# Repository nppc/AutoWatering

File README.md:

# Periodic watering
Simple periodic watering controller
With OLED 96x16 pixels.

Two states of operation.
Waiting (configurable, max 99 hours and 59 minutes)
While waiting after 3 minutes of state change it goes to savescreen mode.
In this mode you see the random dots. Dots quantity is minutes remaining (but not more than 40 dots).

Watering (configurable, max 99 minutes and 59 seconds)
While watering low mosfet is turned on.

## Configuration
Press and hold button until wait time start blink. If you need to adjust watering time, then hold button longer.

With short presses change number 1 by 1. With long press - numbers is running.
If button is not pressed for more than 3 seconds, then next number will be available for adjust.

New time is stored in eeprom.

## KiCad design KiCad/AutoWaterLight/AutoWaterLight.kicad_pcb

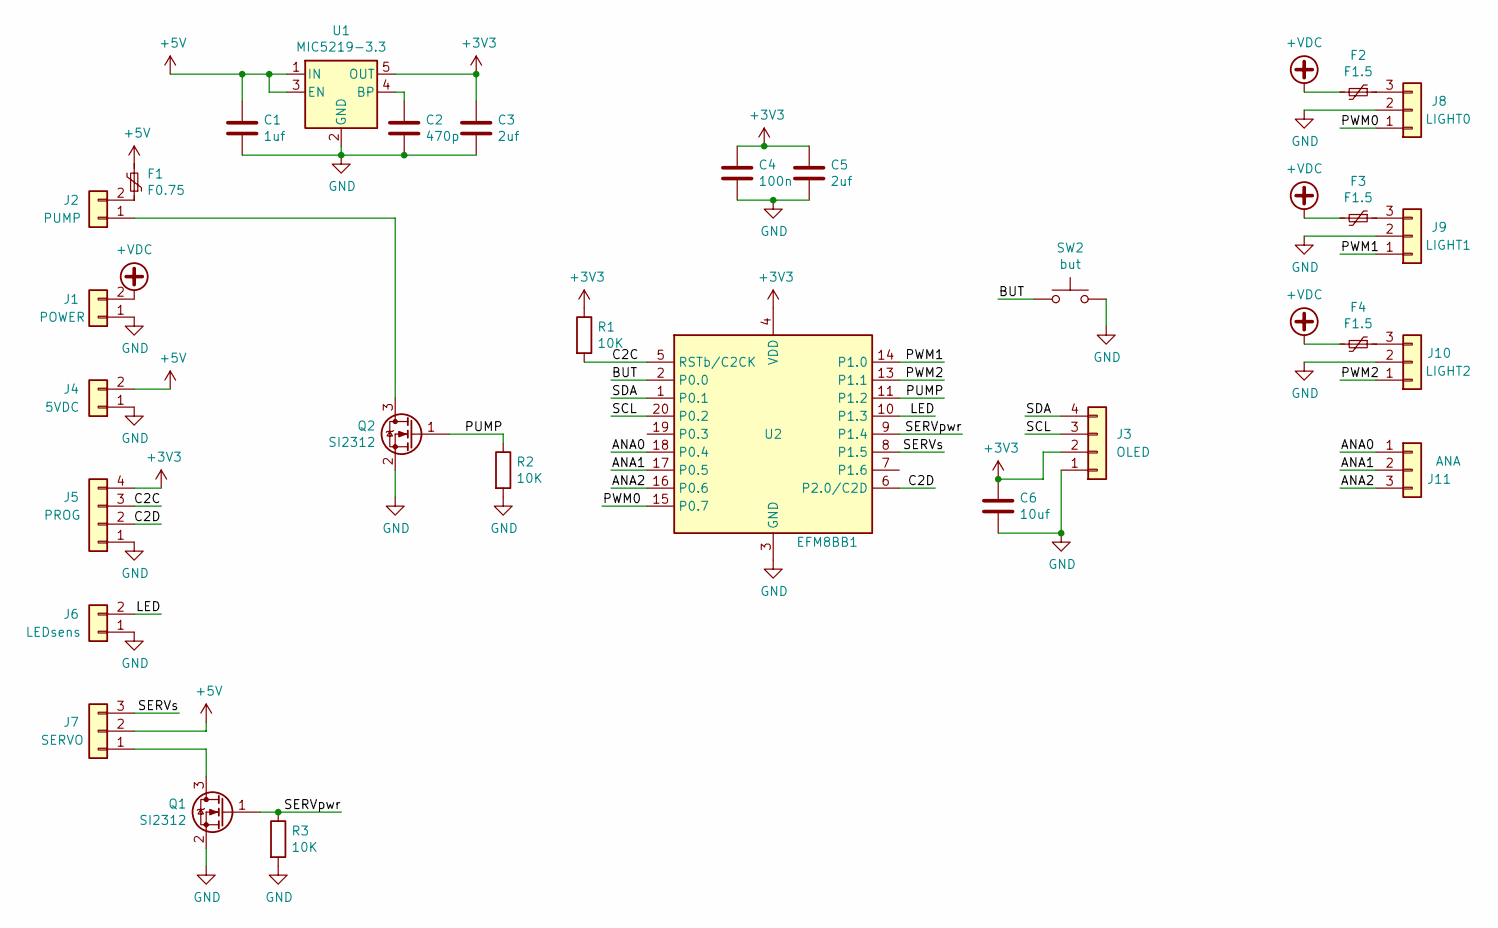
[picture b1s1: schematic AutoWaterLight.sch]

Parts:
C1: 1uf; C_0603
C2: 470p; C_0603
C3, C5: 2uf; C_0603
C4: 100n; C_0603
C6: 10uf; C_0603
F1: F0.75; R_1812
F2, F3, F4: F1.5; R_1812
J1: POWER; Conn_Power
J2: PUMP; Conn_1x02_2.54_0.9mm
J3: OLED; Pin_Header_Straight_1x04_Pitch2.54mm
J4: 5VDC; Conn_1x02_2.54_0.9mm
J5: PROG; Molex_PicoBlade_53047-0410_04x1.25mm_Straight
J6: LEDsens; Conn_1x02_2.54_0.9mm
J7: SERVO; Conn_1x03_2.54mm
J8: LIGHT0; Conn_1x03_2.54mm
J9: LIGHT1; Conn_1x03_2.54mm
J10: LIGHT2; Conn_1x03_2.54mm
J11: ANA; PROG-3pin
Q1, Q2: SI2312; SOT-23
R1, R2, R3: 10K; R_0603
SW2: but; POWER2PIN_2
U1: MIC5219-3.3; SOT-23-5
U2: EFM8BB1; QFN20

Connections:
+3V3: C3.1, C4.1, C5.1, C6.1, J3.2, J5.4, R1.1, U1.5 (OUT), U2.4 (VDD)
+5V: C1.1, F1.2, J4.2, J7.2, U1.1 (IN), U1.3 (EN)
+VDC: F2.2, F3.2, F4.2, J1.2
/ANA0: J11.1, U2.18 (P0.4)
/ANA1: J11.2, U2.17 (P0.5)
/ANA2: J11.3, U2.16 (P0.6)
/BUT: SW2.1, U2.2 (P0.0)
/C2C: J5.3, R1.2, U2.5 (RSTb/C2CK)
/C2D: J5.2, U2.6 (P2.0/C2D)
/LED: J6.2, U2.10 (P1.3)
/PUMP: Q2.1 (G), R2.1, U2.11 (P1.2)
/PWM0: J8.1, U2.15 (P0.7)
/PWM1: J9.1, U2.14 (P1.0)
/PWM2: J10.1, U2.13 (P1.1)
/SCL: J3.3, U2.20 (P0.2)
/SDA: J3.4, U2.1 (P0.1)
/SERVpwr: Q1.1 (G), R3.1, U2.9 (P1.4)
/SERVs: J7.3, U2.8 (P1.5)
GND: C1.2, C2.2, C3.2, C4.2, C5.2, C6.2, J1.1, J3.1, J4.1, J5.1, J6.1, J8.2, J9.2, J10.2, Q1.2 (S), Q2.2 (S), R2.2, R3.2, SW2.2, U1.2 (GND), U2.3 (GND), U2.12 (GND), U2.21 (GND)
unnamed: C2.1, U1.4 (BP)
unnamed: F1.1, J2.2
unnamed: F2.1, J8.3
unnamed: F3.1, J9.3
unnamed: F4.1, J10.3
unnamed: J2.1, Q2.3 (D)
unnamed: J7.1, Q1.3 (D)

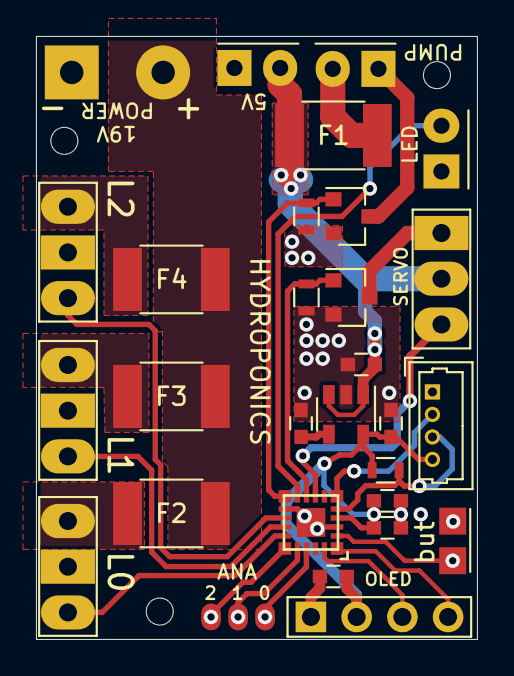
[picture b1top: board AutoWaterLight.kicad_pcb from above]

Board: 2 copper layers, 24.5 x 33.5 mm, 29 parts (0 on the bottom side), 26 nets.

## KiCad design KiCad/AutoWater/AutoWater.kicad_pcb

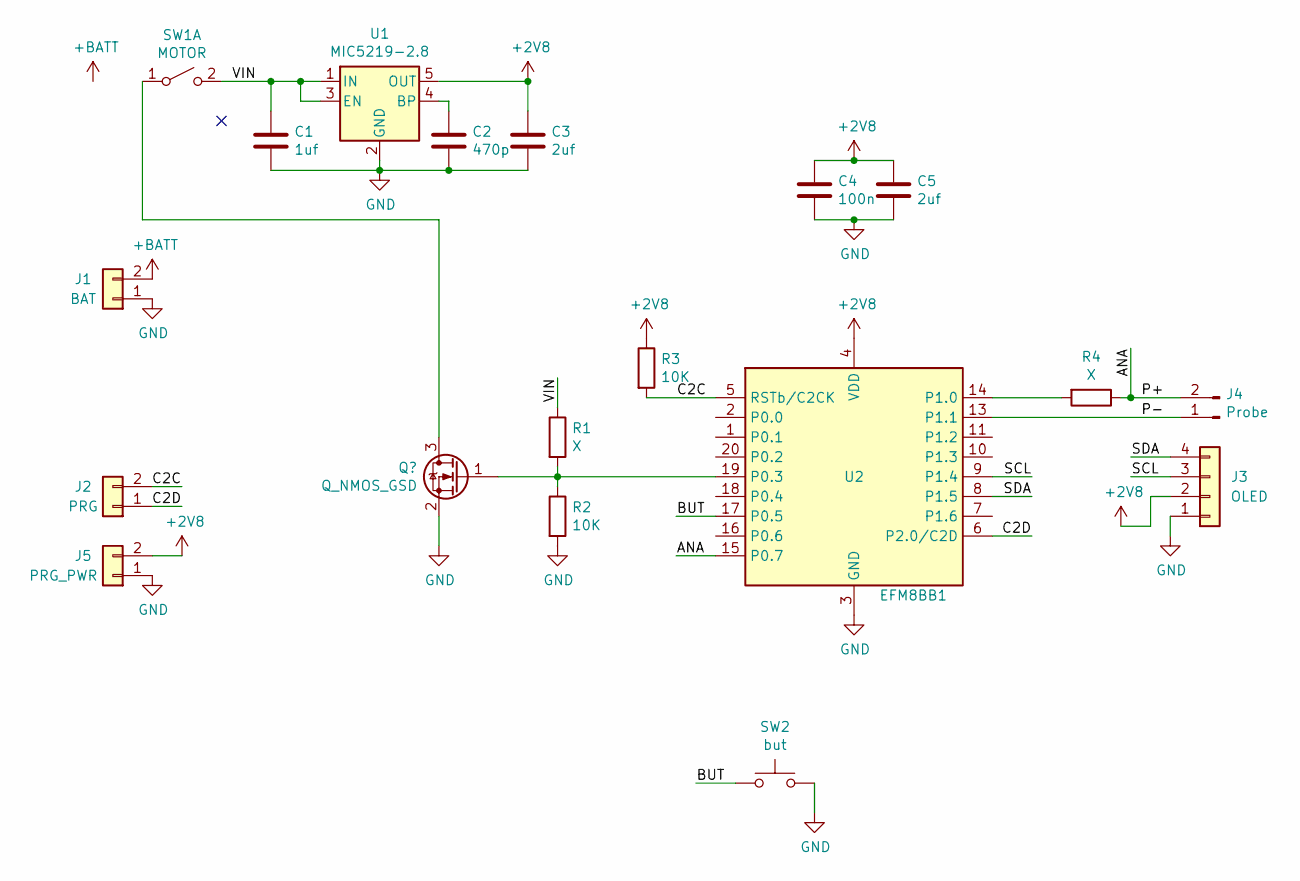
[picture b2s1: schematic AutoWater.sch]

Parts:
C1: 1uf; C_0603
C2: 470p; C_0603
C3, C5: 2uf; C_0603
C4: 100n; C_0603
J1: BAT; Conn_1x02_2.54_0.9mm
J2: PRG; POWER2PIN_2
J3: OLED; Pin_Header_Straight_1x04_Pitch2.54mm
J4: Probe; POWER2PIN_2
J5: PRG_PWR; POWER2PIN_2
R1, R4: X; R_0603
R2, R3: 10K; R_0603
SW1: MOTOR; Conn_1x02_2.54_0.9mm
SW2: but; POWER2PIN_2
U1: MIC5219-2.8; SOT-23-5
U2: EFM8BB1; QFN20

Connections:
+2V8: C3.1, C4.1, C5.1, J3.2, J5.2, R3.1, U1.5 (OUT), U2.4 (VDD)
+BATT: J1.2, SW1.1 (A)
/ANA: J4.2, R4.1, U2.15 (P0.7)
/BUT: SW2.1, U2.17 (P0.5)
/C2C: J2.2, R3.2, U2.5 (RSTb/C2CK)
/C2D: J2.1, U2.6 (P2.0/C2D)
/P-: J4.1, U2.13 (P1.1)
/SCL: J3.3, U2.9 (P1.4)
/SDA: J3.4, U2.8 (P1.5)
/VIN: C1.1, R1.1, SW1.2 (B), U1.1 (IN), U1.3 (EN)
GND: C1.2, C2.2, C3.2, C4.2, C5.2, J1.1, J3.1, J5.1, R2.2, SW2.2, U1.2 (GND), U2.3 (GND), U2.12 (GND), U2.21 (GND)
unnamed: C2.1, U1.4 (BP)
unnamed: R1.2, R2.1, U2.19 (P0.3)
unnamed: R4.2, U2.14 (P1.0)

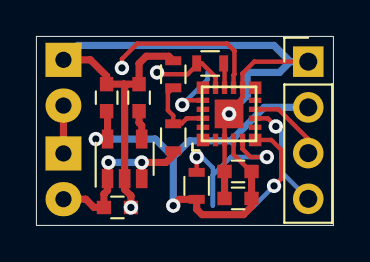
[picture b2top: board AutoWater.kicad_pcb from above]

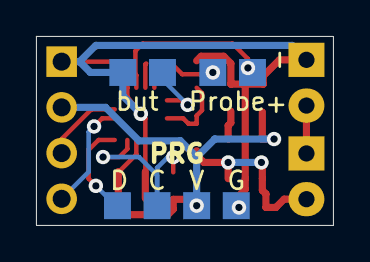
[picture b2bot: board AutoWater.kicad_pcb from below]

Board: 2 copper layers, 16.5 x 10.5 mm, 18 parts (4 on the bottom side), 14 nets.

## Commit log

2021-07-16 ignore debug
2021-07-16 Add images
2021-07-16 Implement software image scrolling
2021-07-16 scroll bitmap is working
2021-07-16 Display timers
2021-07-16 timers working
2021-07-18 PCB bottom side
2021-07-19 Screen Saver part I
2021-07-20 Config part 1
2021-07-20 Config implementation 2
2021-07-20 Config short press done
2021-07-21 Config button long press
2021-07-21 Config done
2021-07-22 ScreenSaver Part 2
2021-07-22 implement bubble sort
2021-07-23 ScreenSaver test
2021-07-23 screen saver routines are working
2021-07-23 add screen saver to main routine
2021-07-23 Screen Saver is fully working
2021-08-16 complete device photos
2021-08-16 Description added
2021-08-28 Add auto watering light project
2021-10-08 Version for efm8bb21
2021-10-09 Simplify pwm control
2021-10-13 nums
2021-10-18 light working
2021-10-18 small refinments
2021-10-22 light sensor
2021-10-23 dazlight logic
2021-10-23 daylight logic is working
2021-10-25 latest changes
2021-10-25 fix issue with light if there is night outside
2021-10-25 fix issue with not updating the timer right away
2021-11-04 new font
2021-11-04 new font etc
2021-11-04 move config routines
2021-11-07 Combine all 3 pwm outs
2021-11-09 two lamps is working
2021-11-12 Add Light icon
2021-11-12 Exit from Config after save
2021-11-12 small font working
2021-11-12 cosmetic changes
2021-11-20 ECOM disable for ch1 and ch2
2021-12-19 differentiate MORNING and NIGHT
2021-12-21 Longer time for On/Off
2021-12-21 Add kalman filter
2021-12-21 Kalman is added to light sensor
2021-12-23 Prefill Kalman variables
2021-12-24 fix morning/night
2022-01-11 Move PWM routines from Interrupts to main loop
2022-01-11 make light on/off slower
2022-01-24 Simplified day/night logic
2022-01-24 turn on/off leds on button
